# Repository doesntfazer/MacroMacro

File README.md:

# MacroMacro
a large gaming macro pad that runs on Vial

If you're looking to build one of your own, you can upload the **Macropad-gerber.zip** from the **gerber** folder to JLCPCB. 

If you don't feel like sodering diodes, you can upload the File in the **BOM** folder, along with the **macropad-bottom-pos.csv** in the **PIP** folder. 

You will need to solder in your hot swap sockets though. I didn't use a hot-swap Footprint that was ready for manufacturing, unfortunately. You're welcome to do this if you want to have everything but the MCU assembled by JLCPCB.

This uses a Waveshare RP2040 Zero as its MCU. Please see the image below. As you can see the 2040 is soldered in face down. This is not the conventional way of mounting these. The reason for doing it this way
is to keep the gamepad thin.

The firmware can be found in the "Firmware" folder. All you need to do is hold the boot button down while plugging it in, then you drag and drop the .UF2 file into the "drive"
I have also added the Keyboard folder in case you want to compile it yourself.

as always it will also be in the [Keyboard Dweebs Firmware repository](https://github.com/doesntfazer/Keyboard-Dweebs-Firmware-repository/tree/main) as well. 

Case files for 3d printing can be found in the "3d Models" folder as well.

You can use a soldering iron to push the threaded inserts into the case.

# Parts List
| Part                         | Quantity |
| --------                     | -------  |
| PCB                          | x1       |
| 1N4148W SOD-123 Diodes       | x51      |
| Kailh Hot Swap Sockets       | x51      |
|Cherry MX Switches            | x51      |
|M2x4mmx3.5mm Threaded inserts | x7       |
| Case                         | x1       |
| Plate                        | x1       |
| M2x10 Screws                 | x5       |
| M2x6 Screws                  | x2       |

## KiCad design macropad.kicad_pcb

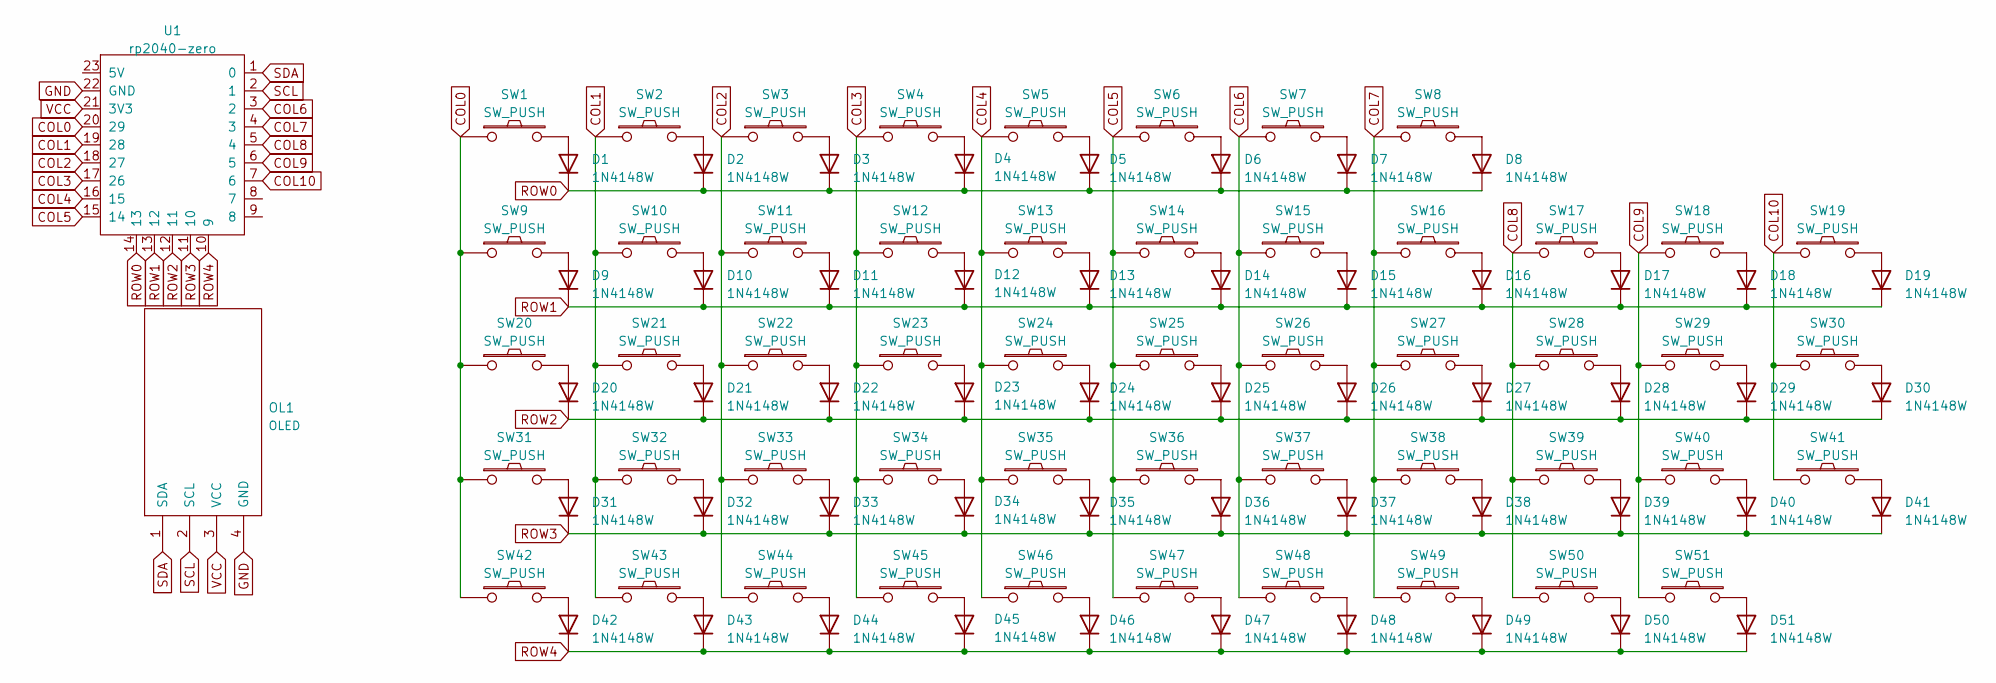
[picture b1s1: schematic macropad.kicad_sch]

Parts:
D1, D2, D3, D4, D5, D6, D7, D8, D9, D10, D11, D12, D13, D14, D15, D16, D17, D18, D19, D20, D21, D22, D23, D24, D25, D26, D27, D28, D29, D30, D31, D32, D33, D34, D35, D36, D37, D38, D39, D40, D41, D42, D43, D44, D45, D46, D47, D48, D49, D50, D51: 1N4148W; D_SOD-123
OL1: OLED; OLED_v2
SW1, SW2, SW3, SW4, SW5, SW6, SW7, SW8, SW9, SW10, SW11, SW12, SW13, SW14, SW15, SW16, SW17, SW18, SW19, SW20, SW21, SW22, SW23, SW24, SW25, SW26, SW27, SW28, SW29, SW30, SW31, SW32, SW33, SW34, SW35, SW36, SW37, SW38, SW39, SW40, SW41, SW42, SW43, SW44, SW45, SW46, SW47, SW48, SW49, SW50, SW51: SW_PUSH; Kailh_socket_MX
U1: rp2040-zero; rp2040-zero-tht-nocut

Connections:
COL0: SW1.1, SW9.1, SW20.1, SW31.1, SW42.1, U1.20 (29)
COL1: SW2.1, SW10.1, SW21.1, SW32.1, SW43.1, U1.19 (28)
COL2: SW3.1, SW11.1, SW22.1, SW33.1, SW44.1, U1.18 (27)
COL3: SW4.1, SW12.1, SW23.1, SW34.1, SW45.1, U1.17 (26)
COL4: SW5.1, SW13.1, SW24.1, SW35.1, SW46.1, U1.16 (15)
COL5: SW6.1, SW14.1, SW25.1, SW36.1, SW47.1, U1.15 (14)
COL6: SW7.1, SW15.1, SW26.1, SW37.1, SW48.1, U1.3 (2)
COL7: SW8.1, SW16.1, SW27.1, SW38.1, SW49.1, U1.4 (3)
COL8: SW17.1, SW28.1, SW39.1, SW50.1, U1.5 (4)
COL9: SW18.1, SW29.1, SW40.1, SW51.1, U1.6 (5)
COL10: SW19.1, SW30.1, SW41.1, U1.7 (6)
GND: OL1.4 (GND), U1.22 (GND)
unnamed: D1.2 (A), SW1.2
unnamed: D2.2 (A), SW2.2
unnamed: D3.2 (A), SW3.2
unnamed: D4.2 (A), SW4.2
unnamed: D5.2 (A), SW5.2
unnamed: D6.2 (A), SW6.2
unnamed: D7.2 (A), SW7.2
unnamed: D8.2 (A), SW8.2
unnamed: D9.2 (A), SW9.2
unnamed: D10.2 (A), SW10.2
unnamed: D11.2 (A), SW11.2
unnamed: D12.2 (A), SW12.2
unnamed: D13.2 (A), SW13.2
unnamed: D14.2 (A), SW14.2
unnamed: D15.2 (A), SW15.2
unnamed: D16.2 (A), SW16.2
unnamed: D17.2 (A), SW17.2
unnamed: D18.2 (A), SW18.2
unnamed: D19.2 (A), SW19.2
unnamed: D20.2 (A), SW20.2
unnamed: D21.2 (A), SW21.2
unnamed: D22.2 (A), SW22.2
unnamed: D23.2 (A), SW23.2
unnamed: D24.2 (A), SW24.2
unnamed: D25.2 (A), SW25.2
unnamed: D26.2 (A), SW26.2
unnamed: D27.2 (A), SW27.2
unnamed: D28.2 (A), SW28.2
unnamed: D29.2 (A), SW29.2
unnamed: D30.2 (A), SW30.2
unnamed: D31.2 (A), SW31.2
unnamed: D32.2 (A), SW32.2
unnamed: D33.2 (A), SW33.2
unnamed: D34.2 (A), SW34.2
unnamed: D35.2 (A), SW35.2
unnamed: D36.2 (A), SW36.2
unnamed: D37.2 (A), SW37.2
unnamed: D38.2 (A), SW38.2
unnamed: D39.2 (A), SW39.2
unnamed: D40.2 (A), SW40.2
unnamed: D41.2 (A), SW41.2
unnamed: D42.2 (A), SW42.2
unnamed: D43.2 (A), SW43.2
unnamed: D44.2 (A), SW44.2
unnamed: D45.2 (A), SW45.2
unnamed: D46.2 (A), SW46.2
unnamed: D47.2 (A), SW47.2
unnamed: D48.2 (A), SW48.2
unnamed: D49.2 (A), SW49.2
unnamed: D50.2 (A), SW50.2
unnamed: D51.2 (A), SW51.2
ROW0: D1.1 (K), D2.1 (K), D3.1 (K), D4.1 (K), D5.1 (K), D6.1 (K), D7.1 (K), D8.1 (K), U1.14 (13)
ROW1: D9.1 (K), D10.1 (K), D11.1 (K), D12.1 (K), D13.1 (K), D14.1 (K), D15.1 (K), D16.1 (K), D17.1 (K), D18.1 (K), D19.1 (K), U1.13 (12)
ROW2: D20.1 (K), D21.1 (K), D22.1 (K), D23.1 (K), D24.1 (K), D25.1 (K), D26.1 (K), D27.1 (K), D28.1 (K), D29.1 (K), D30.1 (K), U1.12 (11)
ROW3: D31.1 (K), D32.1 (K), D33.1 (K), D34.1 (K), D35.1 (K), D36.1 (K), D37.1 (K), D38.1 (K), D39.1 (K), D40.1 (K), D41.1 (K), U1.11 (10)
ROW4: D42.1 (K), D43.1 (K), D44.1 (K), D45.1 (K), D46.1 (K), D47.1 (K), D48.1 (K), D49.1 (K), D50.1 (K), D51.1 (K), U1.10 (9)
SCL: OL1.2 (SCL), U1.2 (1)
SDA: OL1.1 (SDA), U1.1 (0)
VCC: OL1.3 (VCC), U1.21 (3V3)

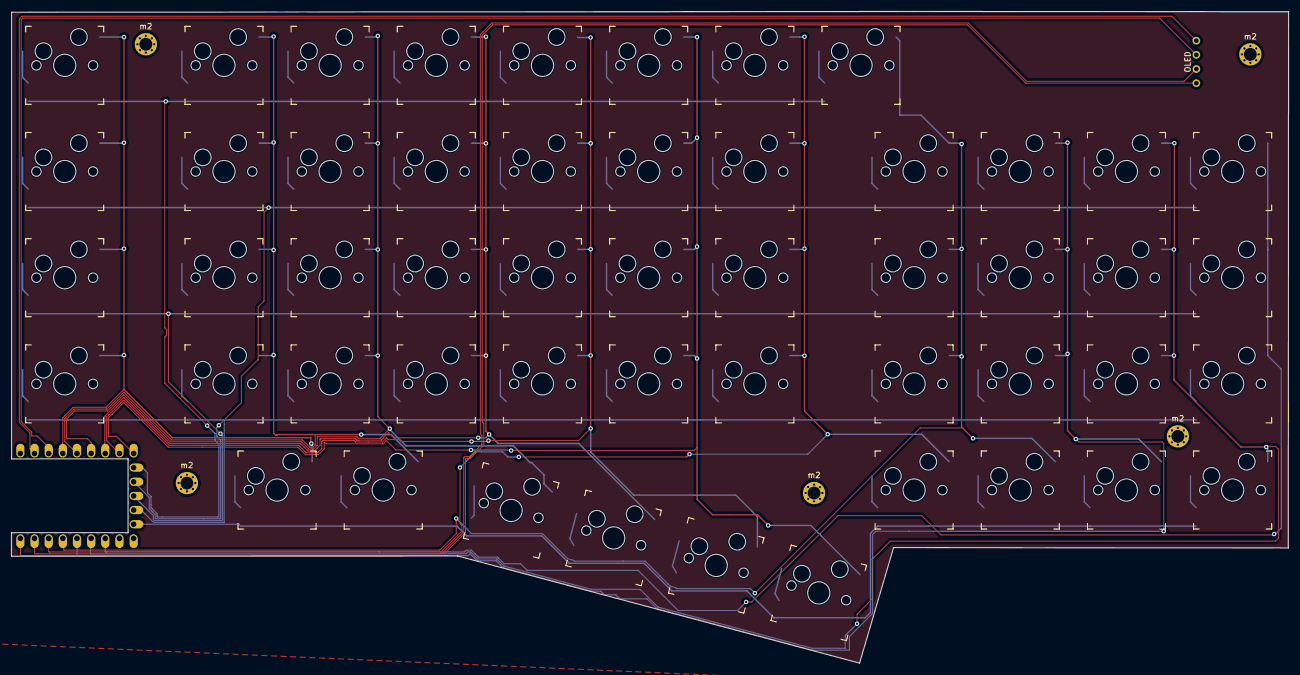
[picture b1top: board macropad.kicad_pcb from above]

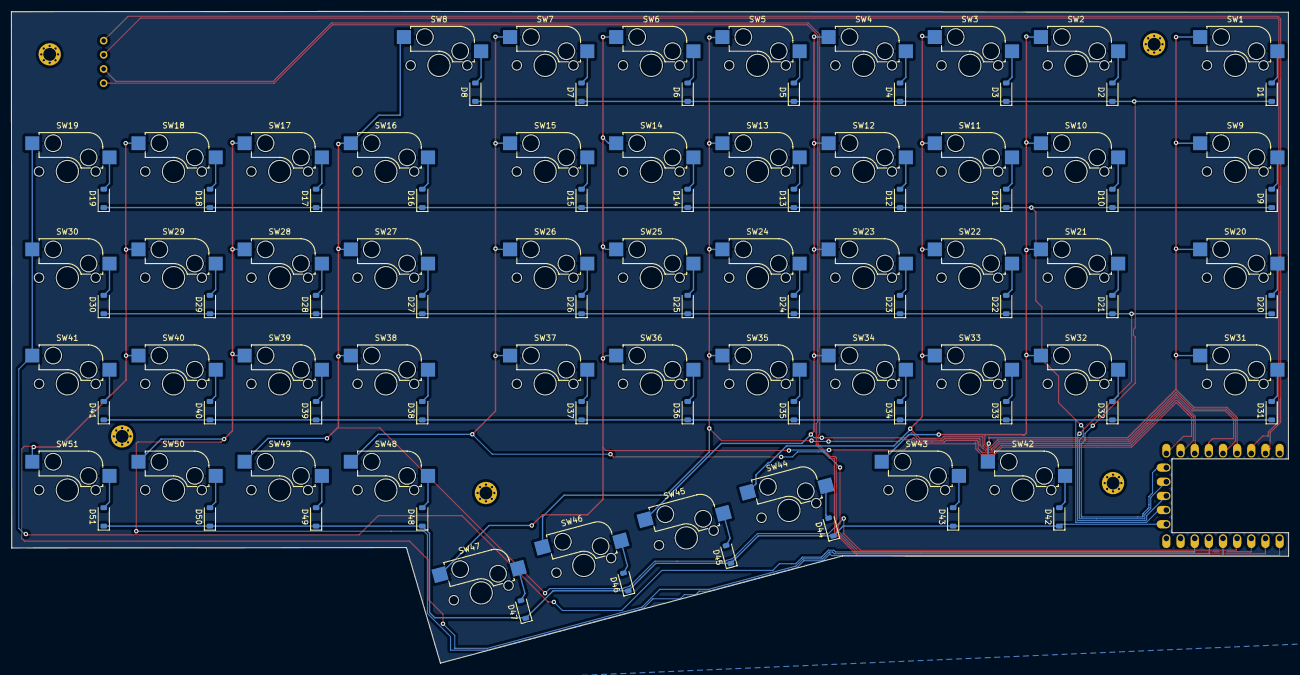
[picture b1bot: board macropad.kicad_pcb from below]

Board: 2 copper layers, 229.2 x 116.9 mm, 109 parts (52 on the bottom side), 71 nets.

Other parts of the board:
m2, m2#2, m2#3, m2#4, m2#5: m2; M2_HOLE_v3

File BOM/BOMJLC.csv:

Comment,Designator,Footprint,LCSC Part #
1N4148W,"D1, D2, D3, D4, D5, D6, D7, D8, D9, D10, D11, D12, D13, D14, D15, D16, D17, D18, D19, D20, D21, D22, D23, D24, D25, D26, D27, D28, D29, D30, D31, D32, D33, D34, D35, D36, D37, D38, D39, D40, D41, D42, D43, D44, D45, D46, D47, D48, D49, D50, D51",D_SOD-123,C81598
SW_PUSH,"SW1, SW2, SW3, SW4, SW5, SW6, SW7, SW8, SW9, SW10, SW11, SW12, SW13, SW14, SW15, SW16, SW17, SW18, SW19, SW20, SW21, SW22, SW23, SW24, SW25, SW26, SW27, SW28, SW29, SW30, SW31, SW32, SW33, SW34, SW35, SW36, SW37, SW38, SW39, SW40, SW41, SW42, SW43, SW44, SW45, SW46, SW47, SW48, SW49, SW50, SW51",Kailh_socket_MX_4fab,C5156480

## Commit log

2023-09-12 added firmware folder
